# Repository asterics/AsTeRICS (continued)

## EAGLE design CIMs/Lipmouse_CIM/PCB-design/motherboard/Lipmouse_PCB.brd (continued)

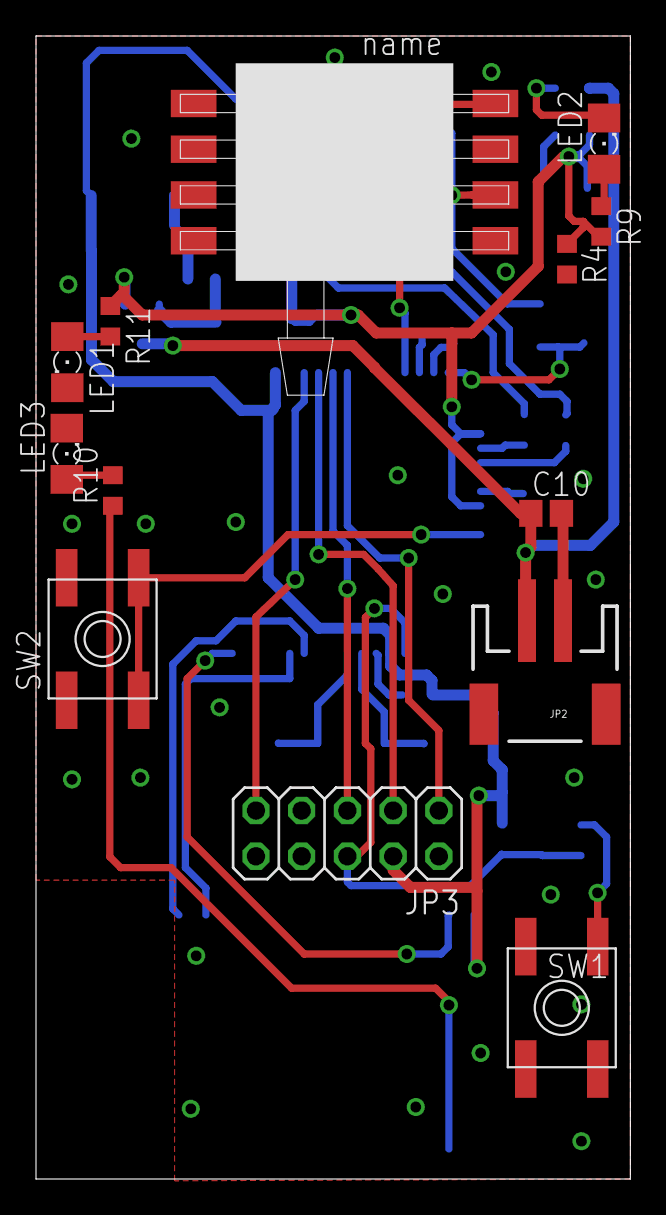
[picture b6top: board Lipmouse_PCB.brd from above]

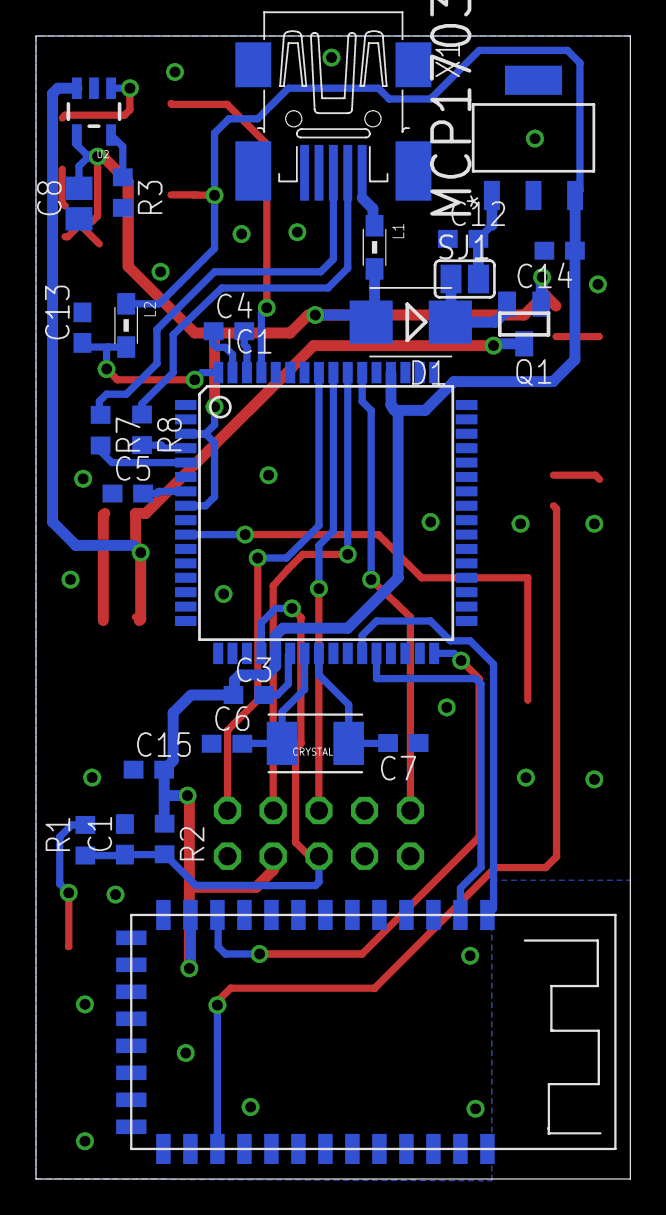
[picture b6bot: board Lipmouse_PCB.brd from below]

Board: 2 copper layers, 33.0 x 63.5 mm, 40 parts (27 on the bottom side), 33 nets.

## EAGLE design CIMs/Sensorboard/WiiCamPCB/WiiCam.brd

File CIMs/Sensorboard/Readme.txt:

AsTeRICS sensorboard CIM, FHTW

The firmware fits for the Atmel AVR AT90USB1286 microcontroller 
(e.g. mounted on the "teensy++" board, see http://www.pjrc.com/store/teensypp.html)

The sensorboard CIM provides a wide range of sensor values from different sources to the AsTeRICS sensorboard plugin.
Depending on the connected sensors, the sensorboard PCB can deliver the following values:
  *) 9 Degree-Of-Freedom IMU data (if the 9-DOF Sensor stick is connected, see: https://www.sparkfun.com/products/10724)
  *) up to 4 infrared led tracking coordinates (x/y each) (if the IR-tracking sensor from a WiiMote device is connected to the I2C bus, see:http://www.instructables.com/id/Wii-Remote-IR-Camera-Hack/?lang=ja)
  *) a pressure sensor value e.g. for a sip/puff sensor (if the MP§V7007GP pressure sensor module is connected)

The sensorboard  can be used for eyetracking, IMU controlled assistive input devices and various other applications.
Please refer to the AsTeRICS user manual and demo models for more information.

Important files/folders:
  firmware/sensorboard.aps:  project file, can be opened/built with AVRStudio 4 + WinAVR
  firmware/sensorboard.hex:  binary/executable, can be downloaded via Atmel FLIP into the microcontroller

  subfolder "WiiCamPCB": schematics/layout files for the GL850 PCB,  featuring:
       the AT90USB1286 microcontroller, 
       mounting options for the Sparkfun SensorsStick + pressure sensor
       I2C connector for the WiiMote IR camera

  subfolder "GL850PCB":  schematics/layout files for the GL850 PCB,  featuring: 
       the AT90USB1286 microcontroller, 
       mounting options for the Sparkfun SensorsStick + pressure sensor
       UART IR-sensor interface (for PAC7001 IR-Cam)
       a USB hub so that a modified webcam for eye-tracking can be connected to the PCB without adding a second USB cable

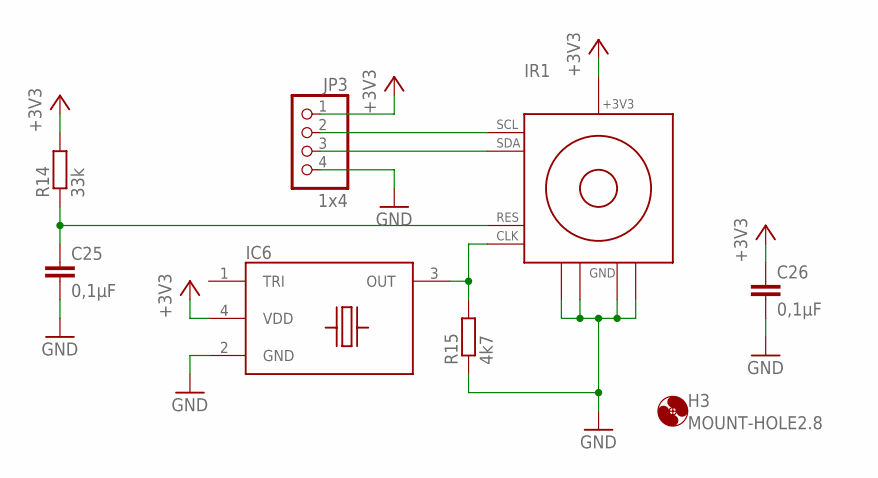
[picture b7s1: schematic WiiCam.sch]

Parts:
C25, C26: 0,1µF; C0805
H3: MOUNT-HOLE2.8; 2,8
IC6: 7W-25.000MBB-T; SMD_7X5MM
IR1: OWN_WII_IR_SENSOR
JP3: 1x4; 1X04
R14: 33k; R0805
R15: 4k7; R0805

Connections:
+3V30: C26.1, IC6.4 (VDD), IR1.1_+3V3 (+3V3), JP3.1, R14.2
GND: C25.2, C26.2, IC6.2 (GND), IR1.2_GND@1 (GND), IR1.3_GND@2 (GND), IR1.GND@3 (GND), IR1.GND@4 (GND), JP3.4, R15.1
OUT: IC6.3 (OUT), IR1.7_CLK (CLK), R15.2
RES: C25.1, IR1.8_RESET (RES), R14.1
SCL1: IR1.5_SCL (SCL), JP3.2
SDA1: IR1.6_SDA (SDA), JP3.3

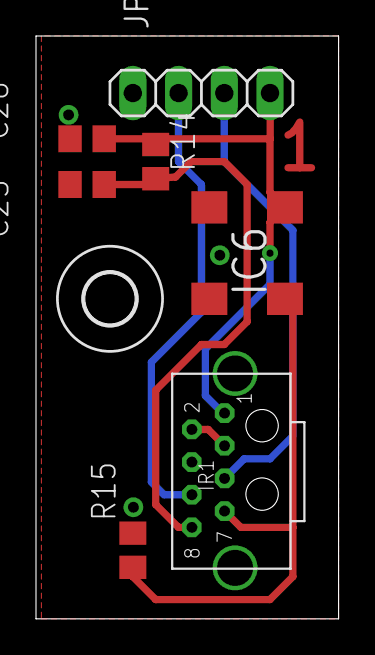
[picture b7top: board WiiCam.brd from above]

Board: 2 copper layers, 16.8 x 32.4 mm, 8 parts (0 on the bottom side), 6 nets.

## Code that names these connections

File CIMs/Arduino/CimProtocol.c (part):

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	  		            if (data_size==2) {
							//check for running PWM
							bitmask = 0xFF;
							if(is_active_PWM(3)) bitmask &= ~(1<<PD3);
							if(is_active_PWM(6)) bitmask &= ~(1<<PD5);
							if(is_active_PWM(5)) bitmask &= ~(1<<PD6);
							
							if(servo3_en) bitmask &= ~(1<<PD3);
							if(servo5_en) bitmask &= ~(1<<PD5);
							if(servo6_en) bitmask &= ~(1<<PD6);
							
							PORTD=ARE_frame.data[0] & bitmask;
							PORTB=ARE_frame.data[1];
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	  		            if (data_size==2) {
							//check for running PWM
							bitmask = 0xFF;
							if(is_active_PWM(3)) bitmask &= ~(1<<PD3);
							if(is_active_PWM(5)) bitmask &= ~(1<<PD5);
							if(is_active_PWM(6)) bitmask &= ~(1<<PD6);
							
							if(servo3_en) bitmask &= ~(1<<PD3);
							if(servo5_en) bitmask &= ~(1<<PD5);
							if(servo6_en) bitmask &= ~(1<<PD6);
							
							PIND_Mask=ARE_frame.data[0] & bitmask;
							PINB_Mask=ARE_frame.data[1];
				 		  
							PCMSK0 = ARE_frame.data[1] & 0x3F; //enable pin change sensing on pins PB0-PB5 (PB6-7 are not connected)
							PCMSK2 = ARE_frame.data[0] & bitmask; //pin change sensing enable on port D
				 		  
						} else status_code |= CIM_ERROR_INVALID_FEATURE;
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											disable_PWM(3);
											servo3_en = 1;
											servo[0] = ARE_frame.data[1] * 79 + 13000; //extend range to timer values
											DDRD |= (1<<PD3);
											enable_servo_ISR();
										break;
										
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											disable_PWM(5);
											servo5_en = 1;
											servo[1] = ARE_frame.data[1] * 79 + 13000; //extend range to timer values
											DDRD |= (1<<PD5);
											enable_servo_ISR();
										break;
										
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											disable_PWM(6);
											servo6_en = 1;
											servo[2] = ARE_frame.data[1] * 79 + 13000; //extend range to timer values
											DDRD |= (1<<PD6);
											enable_servo_ISR();
										break;
									}
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									switch(ARE_frame.data[0] & 0x0F) //low nibble: selected output pin
									{
										case 0x03: //output pin 3
											DDRD &= ~(1<<PD3);
											PORTD &= ~(1<<PD3);
											servo3_en = 0;
											disable_PWM(3);
											if(!(servo5_en | servo6_en)) disable_servo_ISR();
										break;
										
										case 0x05: //output pin 5
											DDRD &= ~(1<<PD5);
											PORTD &= ~(1<<PD5);
											servo5_en = 0;
											disable_PWM(5);
											if(!(servo3_en | servo6_en)) disable_servo_ISR();
										break;
										
										case 0x06: //output pin 6
											DDRD &= ~(1<<PD6);
											PORTD &= ~(1<<PD6);
											servo6_en = 0;
											disable_PWM(6);
											if(!(servo3_en | servo5_en)) disable_servo_ISR();
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
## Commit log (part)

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2020-04-17 Convert documentation from html to markdown
2020-04-17 Fix typo (emoji injected)
2020-04-17 Rename images, remove unsupported characters
2020-04-17 deleted javacv-1.3.1 jars and MANIFEST file, now using maven to download dependencies
2020-04-17 added .bnd files for each platform and updated build.xml to generate osgi-fied bundles of javacv
    * javacv are resolved and downloaded using the maven artifact resolver ant tasks: https://maven.apache.org/resolver-ant-tasks and the javacv pom.xml file.
    * using bndtools to easily generate osgi-fied jar out of javacv jars: https://bnd.bndtools.org/chapters/390-wrapping.html
    * the old mechanism of merging several jars together is not used any more, instead the opencv*.jars are included into the javacv-*-basic-*.jar file as jar files and referenced via class path
2020-04-17 fixed classpath for plugin compilation, use fileset of javacv jars now
2020-04-17 fixed definition of filesets
2020-04-18 Format markdown files, fix wrong paths
2020-04-20 Minor fixes in plugin documentation
2020-04-20 removed unused (old) build target
2020-04-20 added resizing of image to RESIZE_HEIGHT 75 to improve speed of face detection.
    Thanks to learnopencv and Satya Mallick for this trick
2020-04-21 ignoring javacv dependencies (javacv folder with tons of *.jar files)
2020-04-22 Improved setting protocol value and error msg.
    * Set protocol string with value of protocols[propProtocol]
    * Improved error message in case there is no connection.
2020-04-22 improved screenshots, added hint for item copying
2020-04-22 added targets run-debug and run-quick of the ARE/build.xml file
2020-04-22 added support for actionString input port
    * Now you can send commands like: @OPENHAB: Light_GF_Kitchen_Ceiling,ON or also Light_GF_Kitchen_Ceiling,ON
2020-04-22 changed port to default port of openhab 8080
2020-04-22 improved plugin doc
    * improved description of amazon account setup and amazon device setup
2020-04-22 improved error handling (reconnect), improved protocol selection
    * don't use switch(propProtocol) instead use array
    * use reportDebugInfo on almost all locations
2020-04-23 added link to KI-I
2020-04-23 added some hints for pairing and some links regarding Ikea Tradfri bulbs
2020-04-23 PR330
2020-04-24 changed version number to 4.1
2020-04-24 Fixes #320
    Ensures that the first characater is always uppercase when creating the URL help string.
    This should work for all mentioned plugins (serialSender, enocean,...)
    Only P2_Parser.html should be renamed to P2_parser.html
2020-04-24 * Fixes #320 and loads component collection of ARE by default
    Ensures that the first characater is always uppercase when creating the URL help string.
    This should work for all mentioned plugins (serialSender, enocean,...)
    Only P2_Parser.html should be renamed to P2_parser.html
    * set startup bundle to ..\ARE\web\componentCollections\defaultComponentCollection.abd to load directly the component collection which was generated by the ARE at startup. This should ensure that the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
2020-04-30 Set -Xmx to 256M as the real needed memory is about double size and on an RPi 3 this lead to swapping after some time.
    * Tuning of Java Garbage Collection according to
    * https://docs.oracle.com/javase/10/gctuning/factors-affecting-garbage-collection-performance.htm#JSGCT-GUID-6635C481-AE78-485A-A184-A1709712961A
    * Use -verbose:gc for debugging gc cycles and pause time
    * -Xmx<size> sets the max heap size. According to tests the real memory used is about up to 2*Xmx
2020-04-30 switched to WebACS 1.2.1
2020-04-30 Add plugin categories, refactor home, plugins and solutions pages
2020-04-30 auto format markdown
2020-05-01 1+ ARE instances supported now: if port is busy 8081+NR_TRIES*STEP_SIZE is tried, the same for 8082 and 8083
2020-05-01 fixed links "Local WebACS" and "Online WebACS" now using window.location.origin for explicitly setting areBaseURI
2020-05-03 NR_TRIES_PORT and PORT_STEP_SIZE are now configurable in areProperties
2020-05-03 updated CHANGELOG, ready for alpha release
2020-05-04 Wrap solutions components in client-only, add grid images
2020-05-04 Commited Fixes #320 again, did not worn on other machine
2020-05-04 docs: remove slideshows
2020-05-04 improved formatting of --fix-broken install and added choose of
2020-05-04 updated OpenHAB plugin doc
2020-05-05 downgraded javacv to 1.5, this uses opencv 4.0.1 without openblas dependency.
    * This should reduce the .jar sizes and speed up first-time model deployment
    * To be checked: Mac still supported? Did startup-time for others improve?
2020-05-05 added functions to determine cpu architecture and bitness
    * Could be used to do architecture/bitness dependent tasks
2020-05-05 added creation of bitness-specific jars for windows: javacv-xxx-windows-<x86_64>.jar
2020-05-05 Show error message, if camera device could not be opened
2020-05-05 added plugin property resizeHeight, but seems to make no difference, so if useless don't let it parametrize
2020-05-06 added KI-I plugins for EasyReading project: Plugin Help to be updated
2020-05-06 removed system.out of rescaled image height
2020-05-06 removed resizeHeight property again as it the configuration does not have big impact in the detection quality
2020-05-06 docs: remove prev/next from main plugin page, copy and correct documentation for plugins: BlinkChangeDetector, DateToDouble, HRVRmssdFromRR, JsonParser, StringExtractor, TimestampWriter.
2020-05-06 updated component collection with EasyReading plugins
2020-05-06 updated link to APE and type
2020-05-06 added wildcard for deleting other platforms jars of javacv
2020-05-06 updated tutorial for environmental control
2020-05-07 updated description of Asterics Grid added links to webpage and manual
2020-05-07 updated text for OpenHAB tutorial
2020-05-07 updated text, added image of openhab
2020-05-07 commented out link to image
2020-05-11 Update README.md
    fixed typo
2020-05-12 added webacs-links for single/multi-switch models, add link to ARE/models folder
    relates to #342
2020-05-29 removed Ott and Würdinger from Management
2020-06-02 Added additional exception to catch, working now on Linux
2020-06-15 hole ARE -> whole ARE
2020-12-14 added test model for ClientSocket plugin
2020-12-14 fixed cleanup of ClientSocket. Use clientReader.shutdownNow
2020-12-14 added test models for midi sounds and mouse control
2020-12-17 in ClientSocket plugin: changed 195.xxx ip address to localhost
2021-02-23 Update logos of partners and funding
2021-03-08 Update documentation: split funding section in two
2021-04-23 Minor fix (line 06)
2021-04-26 Minor fix (line 06) (#347)
    Typo fixed by @kant
2021-04-27 Minor fix (paragraph 09) (#349)
2021-04-28 Fixed bold formatting in lines 51 & 52
2021-04-28 Minor proposals (paragraphs 20 & 21)
2021-04-28 fixed tutorial: only support openhab v2.5, fixed links, added animated git
2021-05-03 added hint to use Java 8 and to use addons archive to fix installation problems
2021-05-11 Update links to asterics-docs related descriptions
2021-06-07 areBaseURI https:// on Chrome not working, so changed to http://
    This should work for Chrome, Edge out of the box and for Firefox after adding an exception e.g. by trying to start a solution.
    Also added link for directly downloading the model.
2021-08-23 added model that can be used e.g. to control AsTeRICS Grid using an eyetracker
2021-10-11 Update Arduino.md
    added link to arduino demo and tutorials; added installation instructions and fixed bold formating
2021-10-13 fixed formatting
2021-10-18 fixed bold formatting of output port description
2021-10-18 tutorial model for basic gaming and toy control
2021-10-18 updated alt text for demo image
2021-10-18 added gaming tutorial
2021-10-18 added links to plugins
2021-12-16 Removed log4j library
2022-01-17 fixed link to speech platform 11
2022-01-17 fixed model image: use y coordinates not x coordinates
2022-01-17 added reference to project kissenklang
2022-01-17 resized image to 600 and added alignment center
2022-01-17 changed image size to 800
2022-01-18 added note with link to grid user manual
2022-01-18 added note for grid user manual
2022-01-18 moved blood pressure cuff to example projects
2022-05-25 Added Note for Apple users
    If Apple users just double click the DMG file, an "unverified developer" error occurs. Can be circumvented by pressing the control key first, see: https://support.apple.com/en-gb/guide/mac-help/mh406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
2022-07-21 added donation possibility
2022-09-07 now use link to donation summary page
2022-09-07 changed donation link
2022-09-20 fixed hardcoded absoulte path of irserver cmds, use dirname instead
2022-11-17 Bug fix openhab3 REST API: If the Accept types are not explicitly specified, the request fails with error code 400 or 401
2022-11-23 HTTP authentication was only implemented for HTTP GET, also added it for HTTP POST and item state change
2022-11-28 Update release workflow: install ant
2022-11-28 Update release workflow: specify build file
2022-11-28 Update release workflow: use oracle instead of zulu
2022-11-28 Update release workflow: turn on verbose mode
2022-11-28 Update release workflow: upload build artifact, test installation
2022-11-28 Update release workflow: log version after install
2022-11-28 Update release workflow: download InnoSetup Tool
2022-11-28 Update release workflow: install InnoSetup Tool
2022-11-29 Update release workflow: run exe from absolute path
2022-11-29 Update release workflow: change window image
2022-11-29 Update release workflow: test chocolatey installation
2022-11-29 Update release workflow: run help command
2022-11-29 Update release workflow: add build setup for windows
2022-11-29 Remove call to center splash screen in setup.iss
    Property Center is not available (anymore?, cf. https://jrsoftware.org/ishelp/index.php?topic=isxfunc_createcustomform)
2022-11-29 Update release workflow: rename linux build workflow
2022-11-29 Update release workflow: add workflow for mac
2022-11-29 Update release workflow: install ant, build and upload AsTeRICS (macOS)
2022-11-30 Update release workflow: set java platform manually
2022-11-30 Update release workflow: list content of JAVA_HOME
2022-11-30 Update release workflow: use preinstalled java
2022-12-01 Update release workflow: create directory Contents/Home and link to it
2022-12-01 Update release workflow: set JAVA_HOME manually
2022-12-01 Update release workflow: use oracle jdk
2022-12-01 Update release workflow: move zulu jdk in folder containing Contents/Home
2022-12-01 Update release workflow: rename jobs, streamline names, and windows install step
2022-12-02 Update release workflow: add inputs
2022-12-02 Update release workflow: remove windows systeminfo log
2022-12-02 Update release workflow: schedule release
2022-12-03 Update release workflow: generate version from timestamp
2022-12-03 Update release workflow: build all variants with matrix
2022-12-03 Update release workflow: setup builds for all supported operating systems (dispatch, cron, tag)
2022-12-09 docs: fix markup of documentation for home control processors
2023-02-14 replaced betterplace donation link with opencollective
2023-03-07 fixed link to menu
2023-04-17 fixed opencollective link
2023-04-26 added info about sending hex data to action port
2024-01-08 Update release workflow: update available runners
2024-01-08 Update release workflow: add debug output for artifact download
2024-01-08 Update release workflow: change name pattern for release binaries, update job dependencies
2024-01-08 Update release workflow: remove GitHub runner macos-13
2024-01-20 added TrackIR plugin
2024-01-31 Update AREServices.java
    changed webacs edit model URL to http
2024-01-31 added safety check in case .dll could not be loaded
2024-02-09 added myo plugin
2024-02-11 handle NaN values
2024-02-11 added demo models
2024-06-20 Update Legal-Notice.md
    added up2date info of impressum and added link to impressum of Technikum Wien
2024-06-20 Update About-us.md
    fixed links to outdated research projects
    added link to Technikum Wien as a technical lead.
2024-06-20 Update README.md
    fixed commenting out
2024-06-21 Update README.md
    added link to studyathome project, removed AF
2024-06-24 Update Contribute.md
    Fixed commenting out of donation
2024-09-03 Bump actions/download-artifact from 2 to 4.1.7 in /.github/workflows
    Bumps [actions/download-artifact](https://github.com/actions/download-artifact) from 2 to 4.1.7.
    - [Release notes](https://github.com/actions/download-artifact/releases)
    - [Commits](https://github.com/actions/download-artifact/compare/v2...v4.1.7)
    ---
    updated-dependencies:
    - dependency-name: actions/download-artifact
2024-09-26 removed section for donation including link to asterics foundation
2024-09-26 removed newer windows platforms, only use windows-2019
2024-09-26 only use versions ubuntu-20.04, windows-2019 and macos-12
